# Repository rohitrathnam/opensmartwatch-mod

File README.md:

# opensmartwatch-mod
openSmartwatch project with an ECG frontend 

Part of course lab Electronic System Design

See Report.pdf for more details.

## Schematic

## PCB

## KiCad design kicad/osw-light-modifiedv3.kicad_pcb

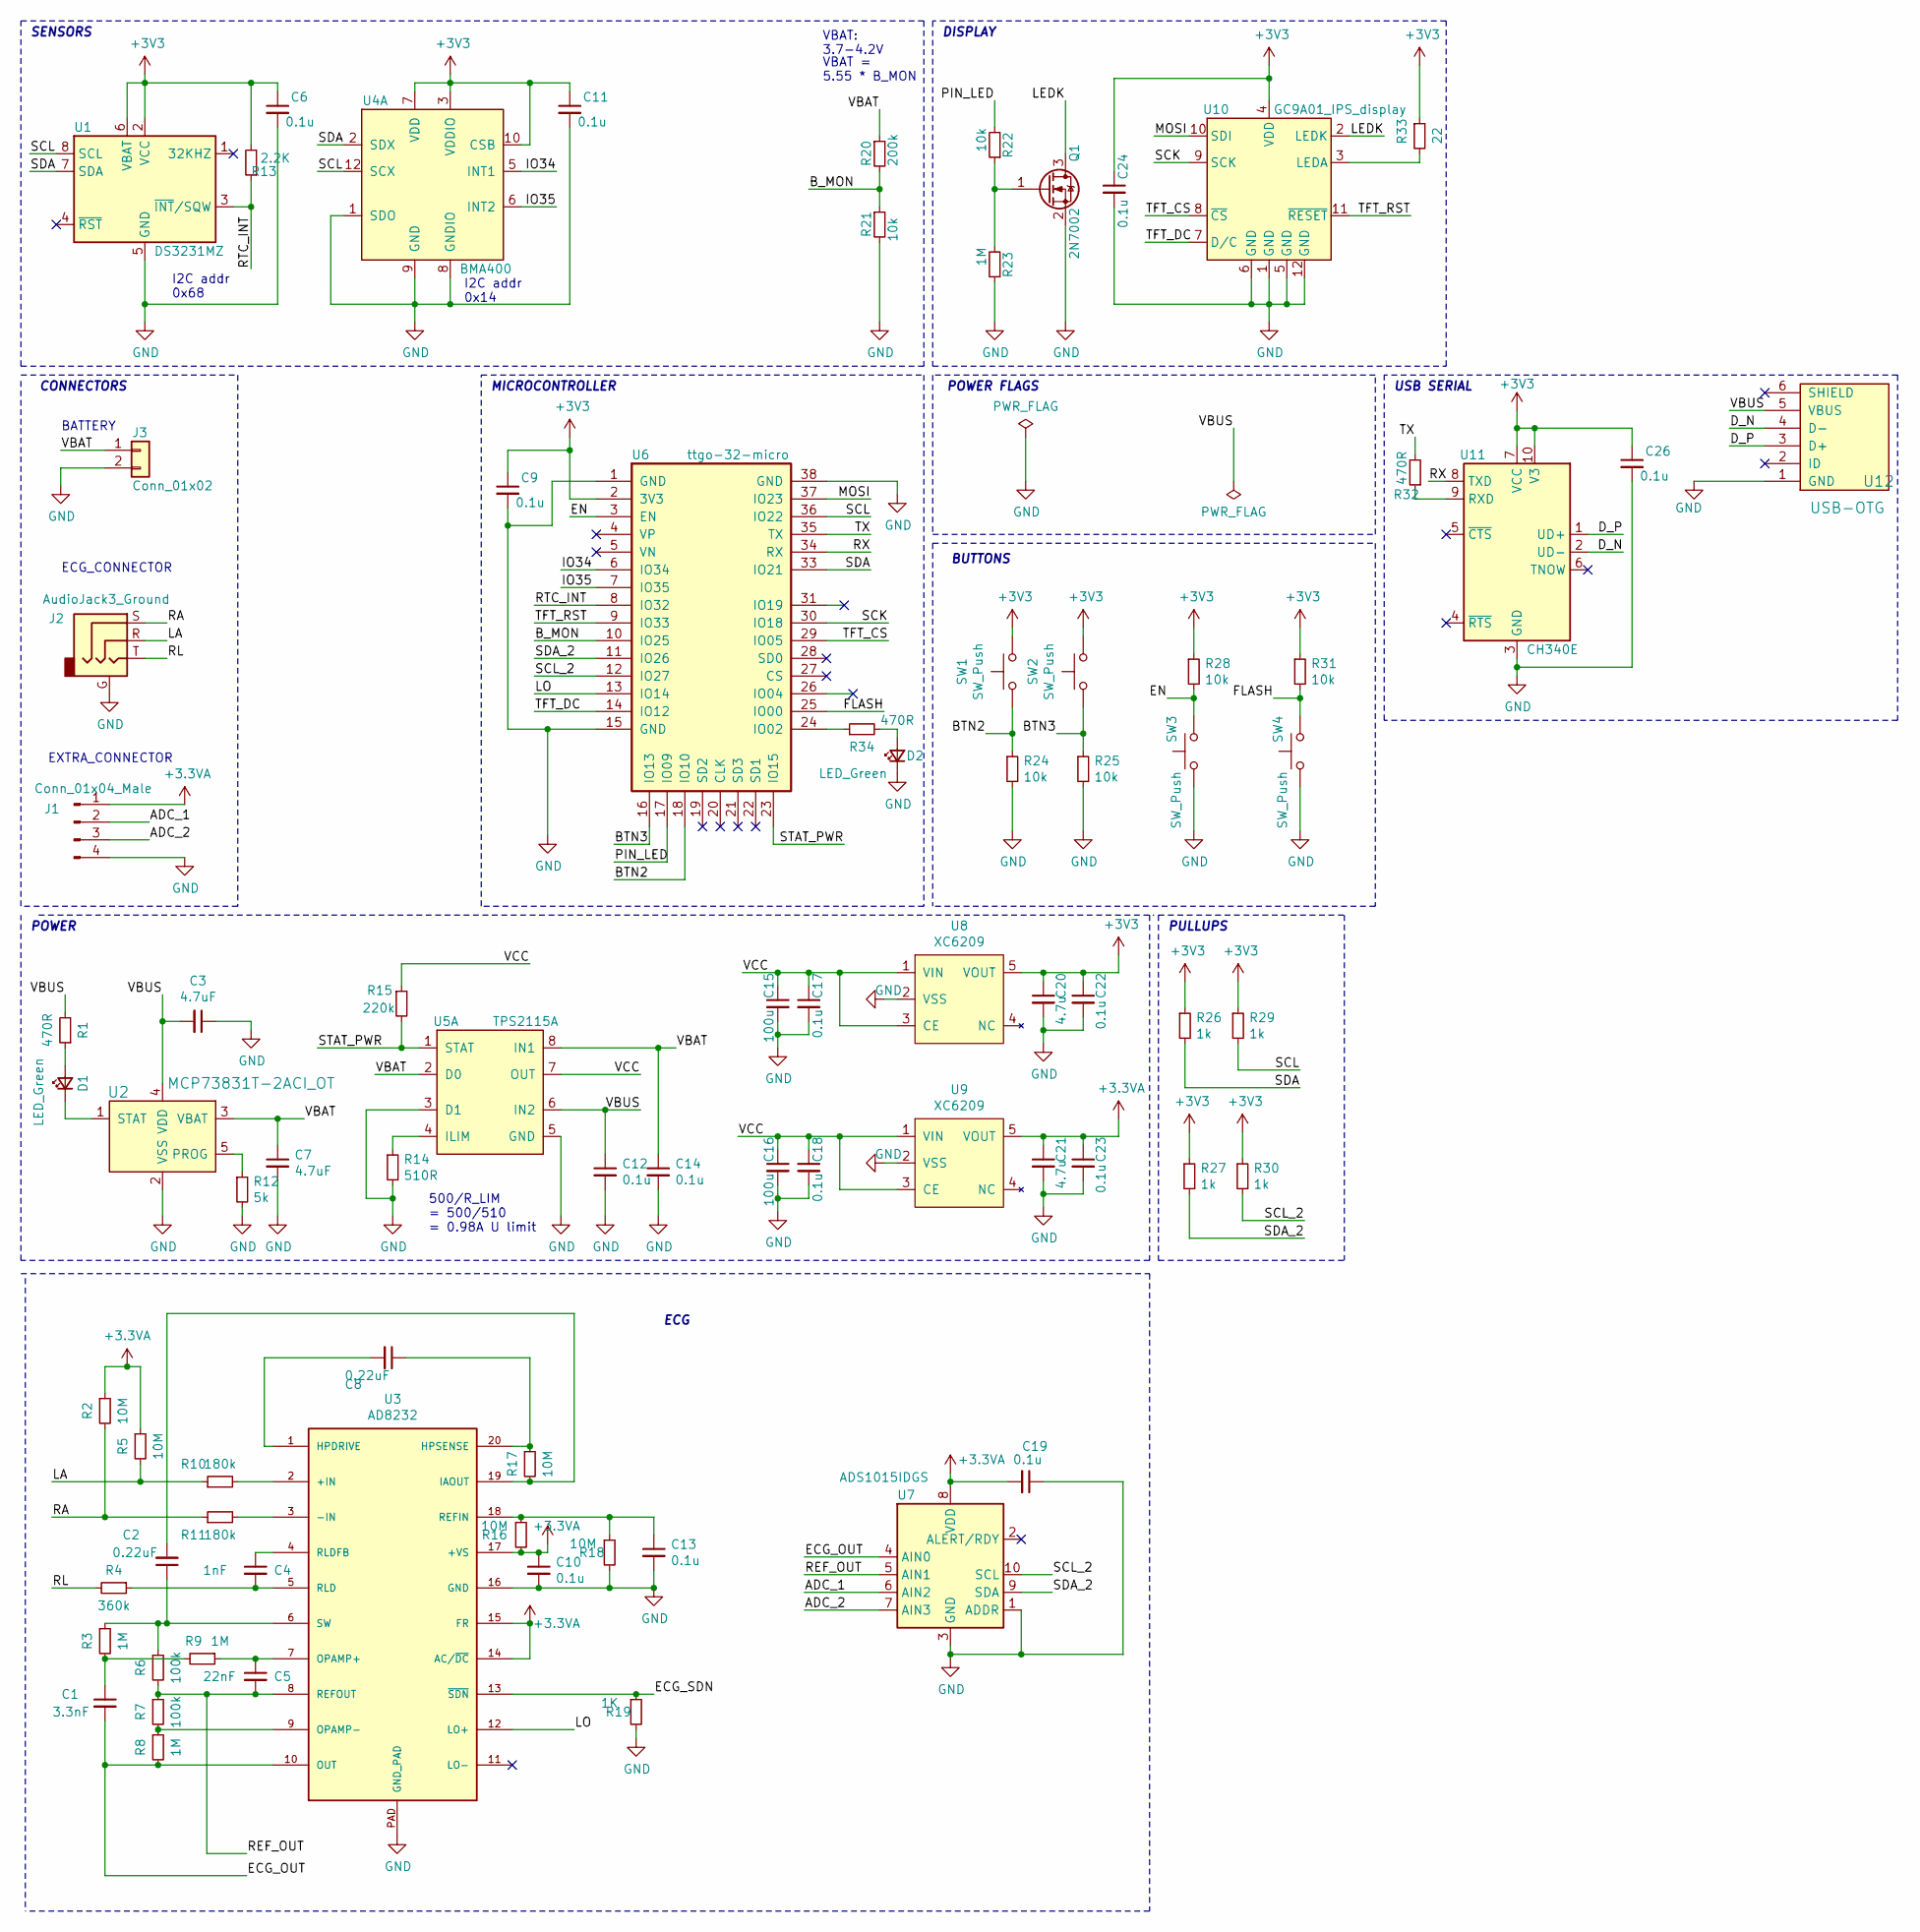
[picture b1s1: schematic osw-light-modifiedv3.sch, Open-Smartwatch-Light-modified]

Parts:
C1: 3.3nF; C_0603_1608Metric
C2, C8: 0.22uF; C_0603_1608Metric
C3, C7: 4.7uF; C_0603_1608Metric
C4: 1nF; C_0603_1608Metric
C5: 22nF; C_0603_1608Metric
C6, C9, C10, C11, C12, C13, C14, C17, C18, C19, C22, C23, C24, C26: 0.1u; C_0603_1608Metric
C15, C16: 100u; C_1206_3216Metric
C20, C21: 4.7u; C_0603_1608Metric
D1, D2: LED_Green; LED_0805_2012Metric
J1: Conn_01x04_Male; PinHeader_1x04_P1.00mm_Vertical_SMD_Pin1Left
J2: AudioJack3_Ground; Jack_3.5mm_CUI_SJ-3524-SMT_Horizontal_mod
J3: Conn_01x02; PinHeader_1x02_P2.54mm_Vertical
Q1: 2N7002; SOT-23
R1, R32, R34: 470R; R_0603_1608Metric
R2, R5, R16, R17, R18: 10M; R_0603_1608Metric
R3, R8, R9, R23: 1M; R_0603_1608Metric
R4: 360k; R_0603_1608Metric
R6, R7: 100k; R_0603_1608Metric
R10, R11: 180k; R_0603_1608Metric
R12: 5k; R_0603_1608Metric
R13: 2.2K; R_0603_1608Metric
R14: 510R; R_0603_1608Metric
R15: 220k; R_0603_1608Metric
R19: 1K; R_0603_1608Metric
R20: 200k; R_0603_1608Metric
R21, R22, R24, R25, R28, R31: 10k; R_0603_1608Metric
R26, R27, R29, R30: 1k; R_0603_1608Metric
R33: 22; R_0603_1608Metric
SW1, SW2, SW3, SW4: SW_Push; button_side_smd
U1: DS3231MZ; SOIC-8_3.9x4.9mm_P1.27mm
U2: MCP73831T-2ACI_OT; SOT-23-5; MPN MCP73831T-2ACI/OT; Digi-Key_PN MCP73831T-2ACI/OTCT-ND
U3: AD8232; LFCSP_20
U4: BMA400; LGA-12_2x2mm_P0.5mm; MPN BMA400; DigiKey_PN 828-1081-1-ND
U5: TPS2115A; TSSOP-8_4.4x3mm_P0.65mm; MPN TPS2115APWR; DigiKey_PN 296-16940-1-ND
U6: ttgo-32-micro
U7: ADS1015IDGS; TSSOP-10_3x3mm_P0.5mm
U8, U9: XC6209; SOT-23-5
U10: GC9A01_IPS_display
U11: CH340E; MSOP-10_3x3mm_P0.5mm
U12: USB-OTG; USBmicro-B

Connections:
+3.3VA: C10.1, C19.2, C21.1, C23.1, J1.1, R2.1, R5.1, R16.2, U3.14 (AC/~DC), U3.15 (FR), U3.17 (+VS), U7.8 (VDD), U9.5 (VOUT)
+3V3: C6.1, C9.1, C11.1, C20.1, C22.1, C24.1, C26.1, R13.2, R26.1, R27.1, R28.1, R29.1, R30.1, R31.1, R33.1, SW1.2, SW2.2, U1.2 (VCC), U1.6 (VBAT), U4.3 (VDDIO), U4.7 (VDD), U4.10 (CSB), U6.2 (3V3), U8.5 (VOUT), U10.4 (VDD), U11.7 (VCC), U11.10 (V3)
/ADC_1: J1.2, U7.6 (AIN2)
/ADC_2: J1.3, U7.7 (AIN3)
/BTN2: R24.1, SW1.1, U6.18 (IO10)
/BTN3: R25.1, SW2.1, U6.16 (IO13)
/B_MON: R20.2, R21.1, U6.10 (IO25)
/D_N: U11.2 (UD-), U12.4 (D-)
/D_P: U11.1 (UD+), U12.3 (D+)
/ECG_OUT: C1.2, R8.2, U3.10 (OUT), U7.4 (AIN0)
/ECG_SDN: R19.1, U3.13 (~SDN)
/EN: R28.2, SW3.2, U6.3 (EN)
/FLASH: R31.2, SW4.2, U6.25 (IO00)
/IO34: U4.5 (INT1), U6.6 (IO34)
/IO35: U4.6 (INT2), U6.7 (IO35)
/LA: J2.R, R5.2, R10.1
/LEDK: Q1.3 (D), U10.2 (LEDK)
/LO: U3.12 (LO+), U6.13 (IO14)
/MOSI: U6.37 (IO23), U10.10 (SDI)
/PIN_LED: R22.2, U6.17 (IO09)
/RA: J2.S, R2.2, R11.1
/REF_OUT: C5.2, R6.2, R7.1, U3.8 (REFOUT), U7.5 (AIN1)
/RL: J2.T, R4.2
/RTC_INT: R13.1, U1.3 (~INT~/SQW), U6.8 (IO32)
/RX: U6.34 (RX), U11.8 (TXD)
/SCK: U6.30 (IO18), U10.9 (SCK)
/SCL: R29.2, U1.8 (SCL), U4.12 (SCX), U6.36 (IO22)
/SCL_2: R30.2, U6.12 (IO27), U7.10 (SCL)
/SDA: R26.2, U1.7 (SDA), U4.2 (SDX), U6.33 (IO21)
/SDA_2: R27.2, U6.11 (IO26), U7.9 (SDA)
/STAT_PWR: R15.2, U5.1 (STAT), U6.23 (IO15)
/TFT_CS: U6.29 (IO05), U10.8 (~CS)
/TFT_DC: U6.14 (IO12), U10.7 (D/C)
/TFT_RST: U6.9 (IO33), U10.11 (~RESET)
/TX: R32.2, U6.35 (TX)
/VBAT: C7.1, C14.1, J3.1, R20.1, U2.3 (VBAT), U5.2 (D0), U5.8 (IN1)
/VBUS: C3.2, C12.1, R1.2, U2.4 (VDD), U5.6 (IN2), U12.5 (VBUS)
/VCC: C15.1, C16.1, C17.1, C18.1, R15.1, U5.7 (OUT), U8.1 (VIN), U8.3 (CE), U9.1 (VIN), U9.3 (CE)
GND: C3.1, C6.2, C7.2, C9.2, C10.2, C11.2, C12.2, C13.2, C14.2, C15.2, C16.2, C17.2, C18.2, C19.1, C20.2, C21.2, C22.2, C23.2, C24.2, C26.2, D2.1 (K), J1.4, J2.G, J3.2, Q1.2 (S), R12.2, R14.2, R18.2, R19.2, R21.2, R23.1, R24.2, R25.2, SW3.1, SW4.1, U1.5 (GND), U2.2 (VSS), U3.16 (GND), U3.PAD (GND_PAD), U4.1 (SDO), U4.8 (GNDIO), U4.9 (GND), U5.3 (D1), U5.5 (GND), U6.1 (GND), U6.15 (GND), U6.38 (GND), U7.1 (ADDR), U7.3 (GND), U8.2 (VSS), U9.2 (VSS), U10.1 (GND), U10.5 (GND), U10.6 (GND), U10.12 (GND), U11.3 (GND), U12.1 (GND)
unnamed: C1.1, R3.2, R9.2
unnamed: C2.1, R3.1, R6.1, U3.6 (SW)
unnamed: C2.2, R17.2, U3.19 (IAOUT)
unnamed: C4.1, U3.4 (RLDFB)
unnamed: C4.2, R4.1, U3.5 (RLD)
unnamed: C5.1, R9.1, U3.7 (OPAMP+)
unnamed: C8.1, R17.1, U3.20 (HPSENSE)
unnamed: C8.2, U3.1 (HPDRIVE)
unnamed: C13.1, R16.1, R18.1, U3.18 (REFIN)
unnamed: D1.1 (K), U2.1 (STAT)
unnamed: D1.2 (A), R1.1
unnamed: D2.2 (A), R34.2
unnamed: Q1.1 (G), R22.1, R23.2
unnamed: R7.2, R8.1, U3.9 (OPAMP-)
unnamed: R10.2, U3.2 (+IN)
unnamed: R11.2, U3.3 (-IN)
unnamed: R12.1, U2.5 (PROG)
unnamed: R14.1, U5.4 (ILIM)
unnamed: R32.1, U11.9 (RXD)
unnamed: R33.2, U10.3 (LEDA)
unnamed: R34.1, U6.24 (IO02)

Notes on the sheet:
500/R_LIM = 500/510 = 0.98A U limit
SENSORS
POWER
DISPLAY
USB SERIAL
BUTTONS
PULLUPS
BATTERY
VBAT: 3.7-4.2V
VBAT = 5.55 * B_MON
MICROCONTROLLER
POWER FLAGS
I2C addr 0x68
I2C addr 0x14
CONNECTORS
ECG_CONNECTOR
EXTRA_CONNECTOR
ECG

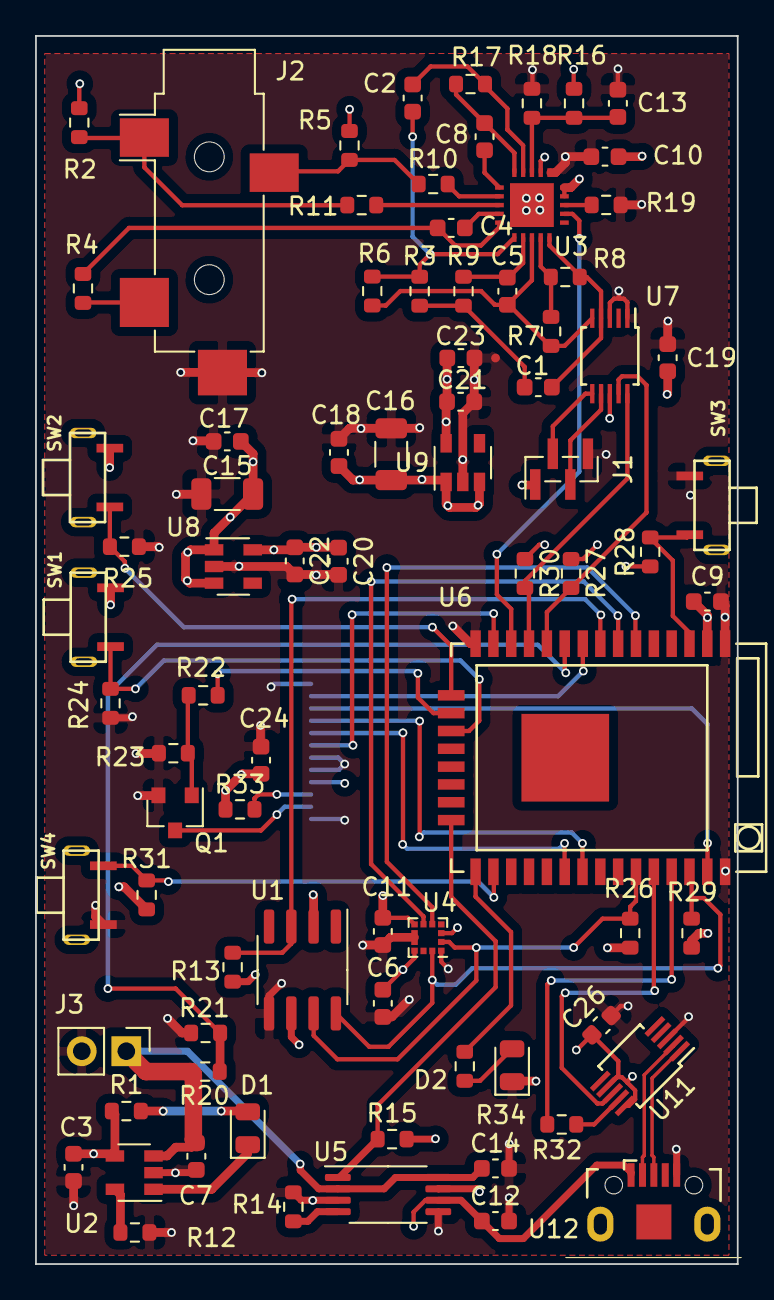
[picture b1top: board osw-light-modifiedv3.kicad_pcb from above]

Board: 4 copper layers, 40.0 x 70.0 mm, 81 parts (1 on the bottom side), 60 nets.

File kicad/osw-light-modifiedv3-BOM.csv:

Reference, Quantity, Value, Footprint,Vendor_PN,Vendor
C1 ,1,3.3nF,Capacitor_SMD:C_0603_1608Metric,2904841,Farnell
C6 C9 C10 C11 C12 C13 C14 C17 C18 C19 C22 C23 C24 C26 ,14,0.1u,Capacitor_SMD:C_0603_1608Metric,1414027,Farnell
C15 C16 ,2,100u,Capacitor_SMD:C_1206_3216Metric,2852714,Farnell
C2 C8 ,2,0.22uF,Capacitor_SMD:C_0603_1608Metric,2905025,Farnell
C20 C21 ,2,4.7u,Capacitor_SMD:C_0603_1608Metric,3217549,Farnell
C4 ,1,1nF,Capacitor_SMD:C_0603_1608Metric,1414025,Farnell
C5 ,1,22nF,Capacitor_SMD:C_0603_1608Metric,1520257,Farnell
C3 C7 ,2,4.7uF,Capacitor_SMD:C_0603_1608Metric,3217549,Farnell
D1 D2 ,2,LED_Green,LED_SMD:LED_0805_2012Metric,2290331,Farnell
J1 ,1,Conn_01x04_Male,Connector_PinHeader_1.00mm:PinHeader_1x04_P1.00mm_Vertical_SMD_Pin1Left,,
J2 ,1,AudioJack3_Ground,open-Smartwatch:Jack_3.5mm_CUI_SJ-3524-SMT_Horizontal_mod,2915138,Farnell
J3 ,1,Conn_01x02,Connector_PinHeader_2.54mm:PinHeader_1x02_P2.54mm_Vertical,,
Q1 ,1,2N7002,Package_TO_SOT_SMD:SOT-23,https://www.aliexpress.com/item/32912312094.html,Aliexpress
R1 R32 R34 ,3,470R,Resistor_SMD:R_0603_1608Metric,2331232,Farnell
R10 R11 ,2,180k,Resistor_SMD:R_0603_1608Metric,2447266,Farnell
R12 ,1,5k,Resistor_SMD:R_0603_1608Metric, PNM0603-5.0KBCT-ND ,Digikey
R13 ,1,2.2K,Resistor_SMD:R_0603_1608Metric,2303166,Farnell
R14 ,1,510R,Resistor_SMD:R_0603_1608Metric,2447392,Farnell
R15 ,1,220k,Resistor_SMD:R_0603_1608Metric,2447297,Farnell
R19 ,1,1K,Resistor_SMD:R_0603_1608Metric,3495238,Farnell
R20 ,1,200k,Resistor_SMD:R_0603_1608Metric,2447291,Farnell
R3 R8 R9 R23 ,4,1M,Resistor_SMD:R_0603_1608Metric,2331023,Farnell
R21 R22 R24 R25 R28 R31 ,6,10k,Resistor_SMD:R_0603_1608Metric,3495224,Farnell
R26 R27 R29 R30 ,4,1k,Resistor_SMD:R_0603_1608Metric,3495238,Farnell
R33 ,1,22,Resistor_SMD:R_0603_1608Metric,2447301,Farnell
R4 ,1,360k,Resistor_SMD:R_0603_1608Metric,3495822,Farnell
R2 R5 R16 R17 R18 ,5,10M,Resistor_SMD:R_0603_1608Metric,2138612,Farnell
R6 R7 ,2,100k,Resistor_SMD:R_0603_1608Metric,3495222,Farnell
SW1 SW2 SW3 SW4 ,4,SW_Push,open-Smartwatch:button_side_smd,https://www.aliexpress.com/item/32870278366.html,Aliexpress
U1 ,1,DS3231MZ,Package_SO:SOIC-8_3.9x4.9mm_P1.27mm,https://www.aliexpress.com/item/32962505279.html,Aliexpress
U10 ,1,GC9A01_IPS_display,open-Smartwatch:GC9A01_IPS_display,https://www.aliexpress.com/item/1005001382307998.html,Aliexpress
U11 ,1,CH340E,open-Smartwatch:MSOP-10_3x3mm_P0.5mm,https://www.aliexpress.com/item/4000171821951.html,Aliexpress
U12 ,1,USB-OTG,open-Smartwatch:USBmicro-B,https://www.aliexpress.com/item/32820570603.html,Aliexpress
U2 ,1,MCP73831T-2ACI_OT,open-Smartwatch:SOT-23-5,2857755,Farnell
U3 ,1,AD8232,LFCSP_20,AD8232ACPZ-R7CT-ND,Digikey
U4 ,1,BMA400,open-Smartwatch:LGA-12_2x2mm_P0.5mm,828-1081-1-ND,Digikey
U5 ,1,TPS2115A,open-Smartwatch:TSSOP-8_4.4x3mm_P0.65mm,3124061,Farnell
U6 ,1,ttgo-32-micro,open-Smartwatch:ttgo-32-micro,https://www.aliexpress.com/item/32869180373.html,Aliexpress
U7 ,1,ADS1015IDGS,Package_SO:TSSOP-10_3x3mm_P0.5mm,3004281,Farnell
U8 U9 ,2,XC6209,Package_TO_SOT_SMD:SOT-23-5,3535214,Farnell
BAT,1,,,https://a.aliexpress.com/_mrvOz8P,Aliexpress
